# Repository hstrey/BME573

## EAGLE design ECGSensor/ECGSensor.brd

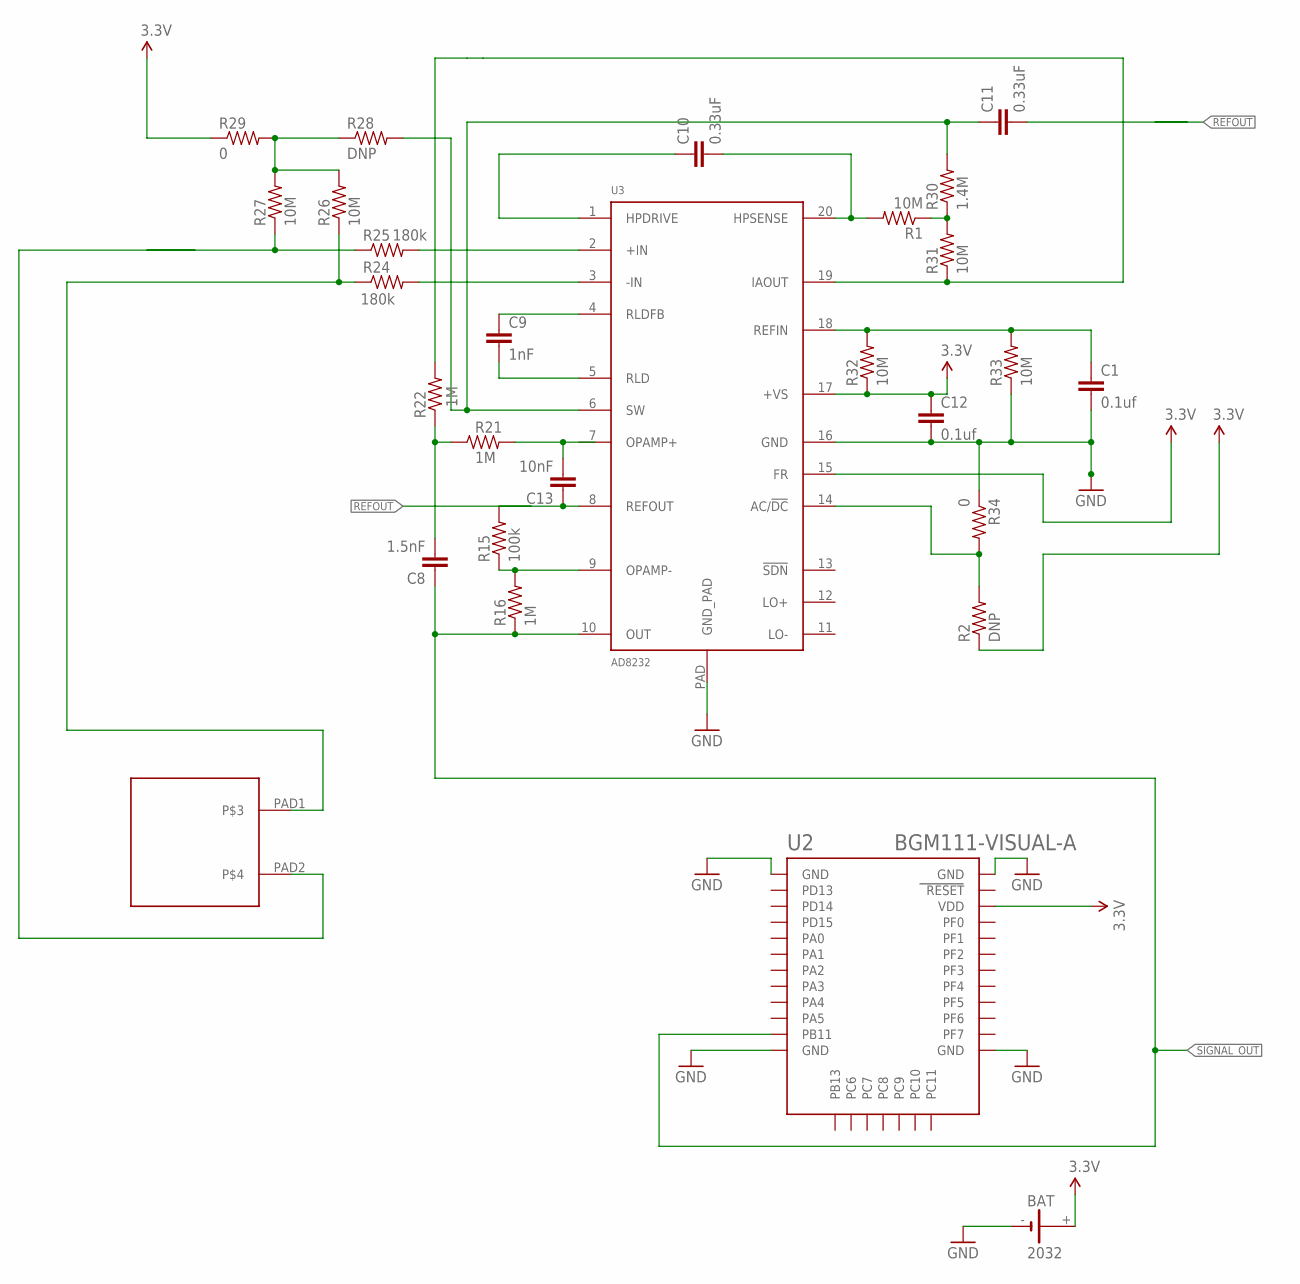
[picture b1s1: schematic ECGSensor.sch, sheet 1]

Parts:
BAT: 2032; KZH20SMD
C1, C12: 0.1uf; 0603-CAP
C8: 1.5nF; 0603-CAP
C9: 1nF; 0603-CAP
C10, C11: 0.33uF; 0805
C13: 10nF; 0603-CAP
R1, R26, R27, R31, R32, R33: 10M; 0603-RES
R2, R28: DNP; 0603
R15: 100k; 0603-RES
R16, R21, R22: 1M; 0603-RES
R24, R25: 180k; 0603-RES
R29, R34: 0; 0603
R30: 1.4M; 0603-RES
U2: BGM111-VISUAL-A; BGM111-A
U3: AD8232; LFCSP_20
U$1: CPAD; SNAPPAD

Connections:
3.3V: BAT.+, C12.1, R2.1, R29.1, R32.1, U2.VDD, U3.15 (FR), U3.17 (+VS)
GND: BAT.-, C1.2, C12.2, R33.1, R34.1, U2.GND, U2.GND@2 (GND), U2.GND@3 (GND), U2.GND@4 (GND), U3.16 (GND), U3.PAD (GND_PAD)
LA: U$1.PAD2
unnamed: C10.1, U3.1 (HPDRIVE)
unnamed: C10.2, R1.2, U3.20 (HPSENSE)
unnamed: R1.1, R30.1, R31.2
unnamed: C11.1, R28.2, R30.2, U3.6 (SW)
unnamed: C1.1, R32.2, R33.2, U3.18 (REFIN)
unnamed: R22.2, R31.1, U3.19 (IAOUT)
unnamed: C9.2, U3.5 (RLD)
unnamed: R2.2, R34.2, U3.14 (AC/!DC)
unnamed: C8.2, R21.1, R22.1
unnamed: C13.2, R21.2
unnamed: C9.1, U3.4 (RLDFB)
unnamed: R24.2, U3.3 (-IN)
unnamed: R25.2, U3.2 (+IN)
unnamed: R25.1, R27.1
unnamed: R24.1, R26.1, U$1.PAD1
unnamed: R26.2, R27.2, R28.1, R29.2
unnamed: R15.1, R16.2, U3.9 (OPAMP-)
unnamed: C13.1, R15.2, U3.8 (REFOUT)
SIGNAL_OUT: C8.1, R16.1, U2.PB11, U3.10 (OUT)

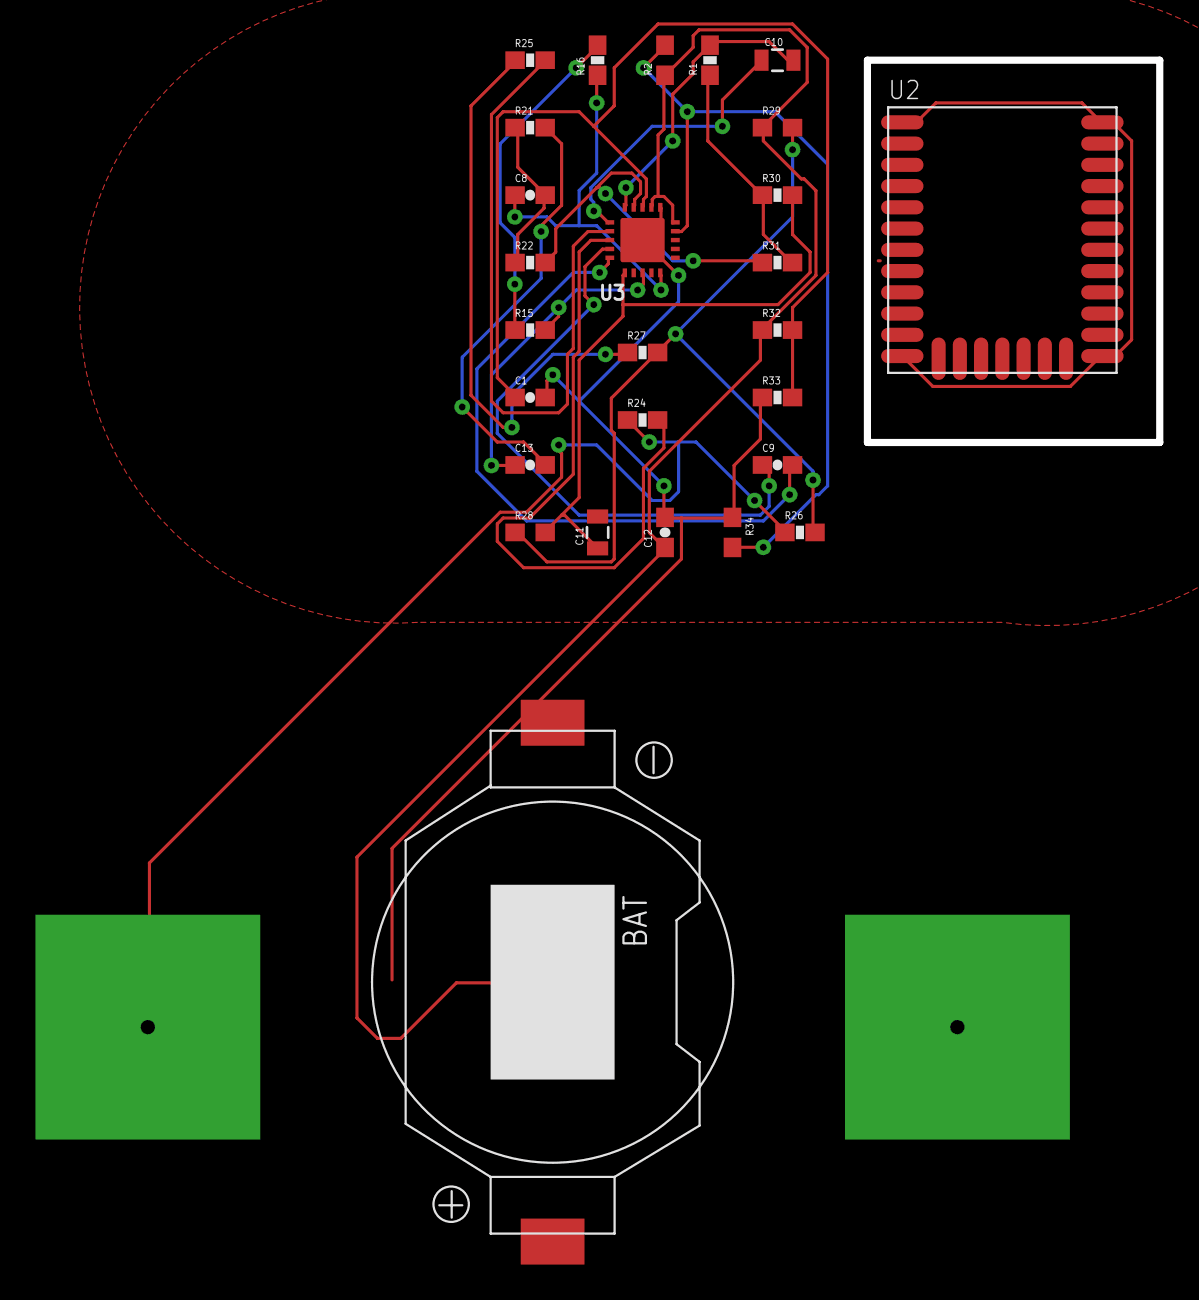
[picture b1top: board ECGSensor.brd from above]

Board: 2 copper layers, 16.5 x 21.6 mm, 28 parts (0 on the bottom side), 21 nets.

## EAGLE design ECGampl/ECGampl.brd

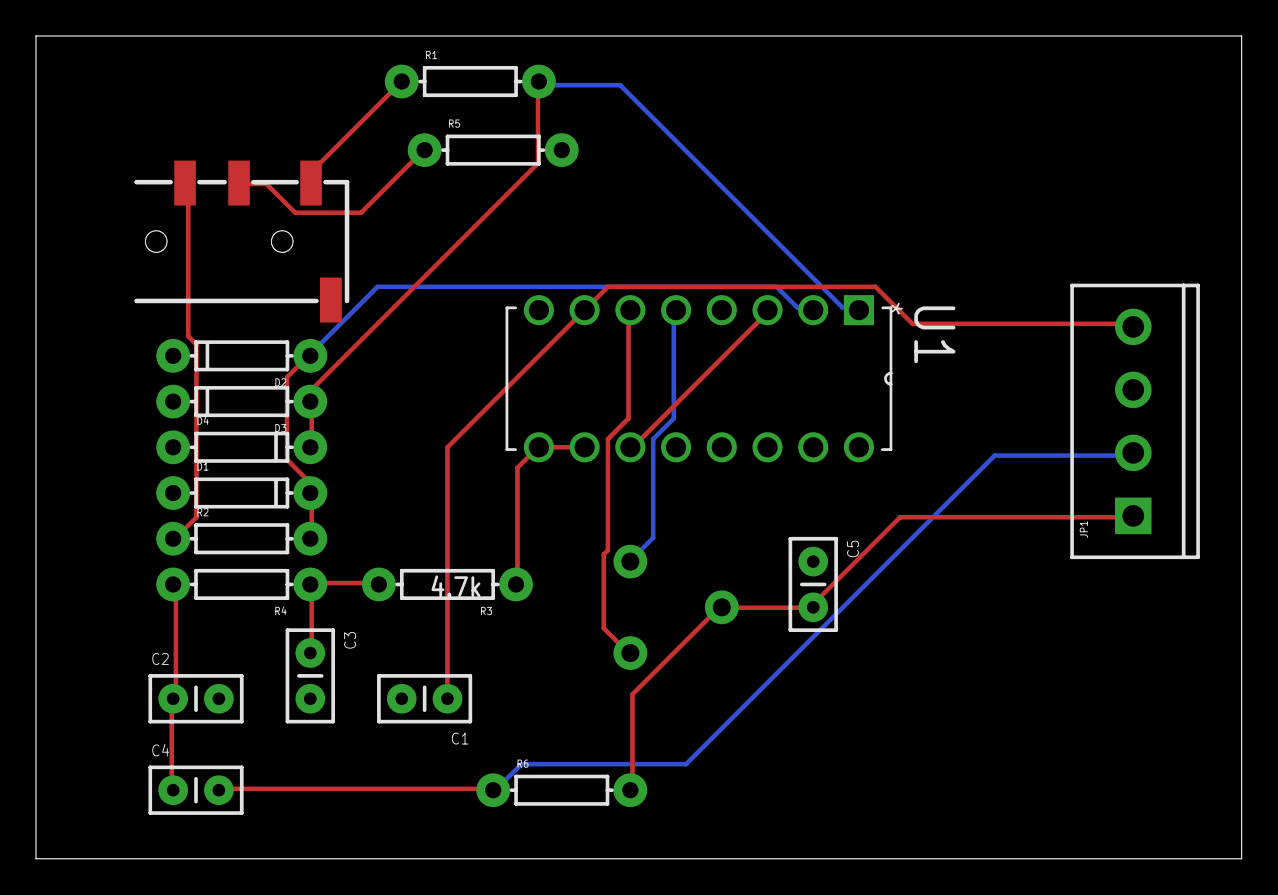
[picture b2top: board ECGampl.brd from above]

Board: 2 copper layers, 67.0 x 45.7 mm, 19 parts (0 on the bottom side), 15 nets.

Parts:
C1, C4, C5: CAP-PTH-SMALLEZ
C2: 0.1uF; CAP-PTH-SMALLEZ
C3: 1.0uF; CAP-PTH-SMALLEZ
D1, D2, D3, D4: DIODE-1N4148
JP1: SCREWTERMINAL-3.5MM-4
R1, R2, R4, R5, R6: AXIAL-0.3
R3: 4.7k; AXIAL-0.3
RV1: TRIM_POT
U1: AD624ADZ; DIP254P775X508-16
U$1: AUDIO-JACK3; AUDIO-JACK-TRRS-SMD

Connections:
GND: C1.2, C2.2, C3.2, C5.1, D1.A, D2.C, D3.C, D4.A, JP1.3, R5.P$2, U1.4
IN1: R1.P$1, U$1.TIP
IN2: R2.P$1, U$1.RING2
unnamed: U1.3, U1.11
unnamed: R3.P$1, U1.9, U1.10
unnamed: C3.1, R3.P$2, R4.P$1
unnamed: C2.1, C4.1, R4.P$2
unnamed: RV1.2, U1.5
unnamed: R5.P$1, U$1.RING1
unnamed: RV1.3, U1.6
unnamed: D1.C, D2.A, R2.P$2, U1.2
unnamed: D3.A, D4.C, R1.P$2, U1.1
unnamed: C4.2, JP1.2, R6.P$1
VDD: C5.2, JP1.1, R6.P$2, RV1.1
VSS: C1.1, JP1.4, U1.7

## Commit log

2016-09-16 added ECGampl eagle files
2016-09-19 corrected some connection errors and placed components on board
2016-09-19 added some component values and fixed some connections
2016-09-19 successful routing
2016-09-20 added draft design for ECG Sensor
2016-11-14 added Simblee sketch for ECG faking
2016-11-14 newest version of Simblee fake ECG

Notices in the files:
parts and their libraries:
SparkFun-Passives: Licensing: CC v3.0 Share-Alike You are welcome to use this library for commercial purposes.
SparkFun-Capacitors: Licensing: Creative Commons ShareAlike 4.0 International - https://creativecommons.org/licenses/by-sa/4.0
